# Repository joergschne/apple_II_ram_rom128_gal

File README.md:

# Apple II 128K RAM + ROM Card - Dual GAL

APPLE II forever!

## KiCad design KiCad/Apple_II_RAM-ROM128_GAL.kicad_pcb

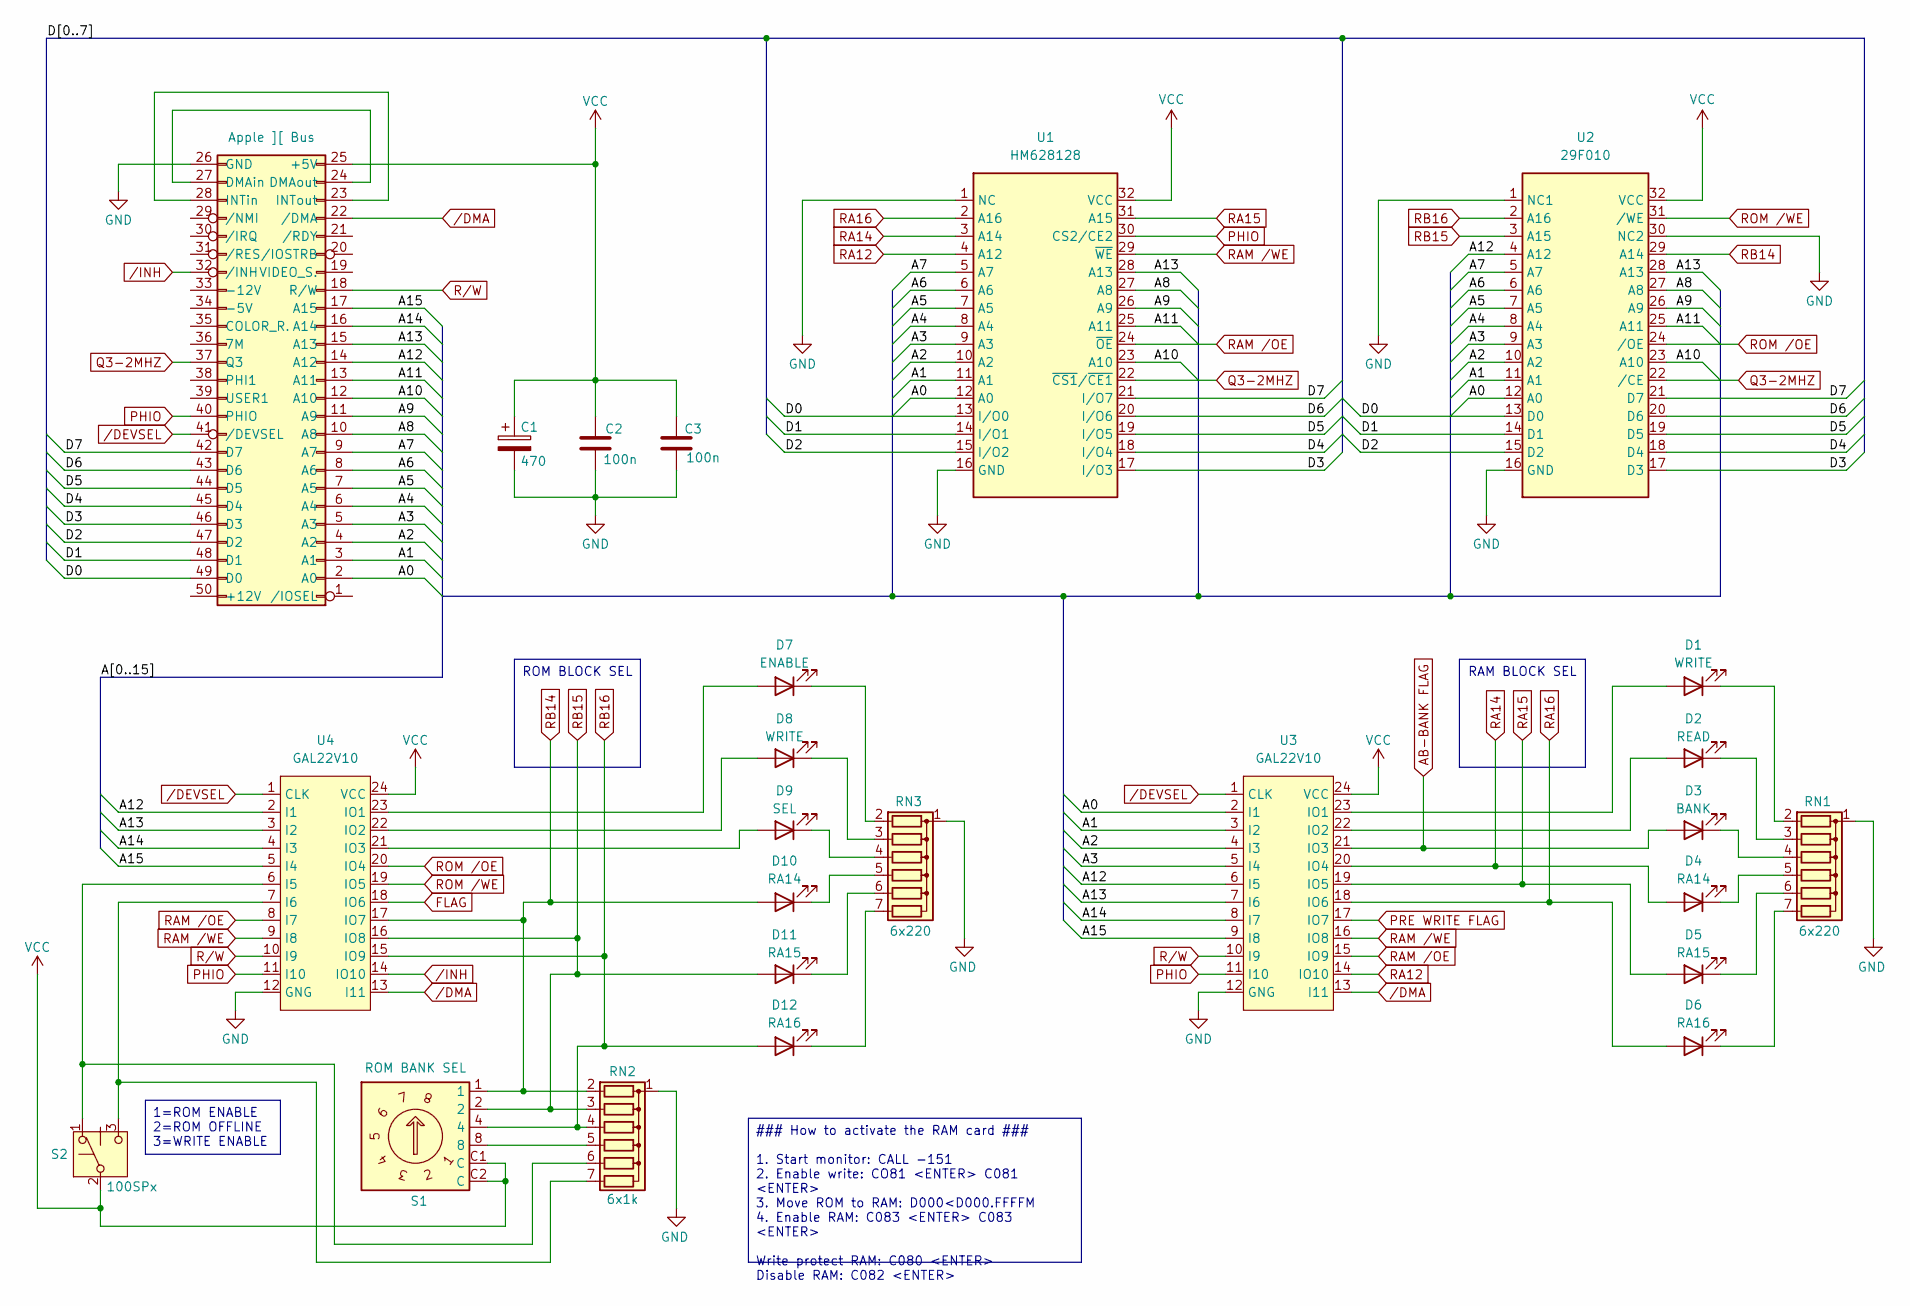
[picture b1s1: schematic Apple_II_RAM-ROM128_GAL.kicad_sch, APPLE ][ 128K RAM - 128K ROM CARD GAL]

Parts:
C1: 470; CP_Radial_D5.0mm_P2.50mm
C2, C3: 100n; C_Rect_L7.0mm_W2.0mm_P5.00mm
D1, D8: WRITE; LED_WP1503CB_GD
D2: READ; LED_WP1503CB_GD
D3: BANK; LED_WP1503CB_GD
D4, D10: RA14; LED_WP1503CB_GD
D5, D11: RA15; LED_WP1503CB_GD
D6, D12: RA16; LED_WP1503CB_GD
D7: ENABLE; LED_WP1503CB_GD
D9: SEL; LED_WP1503CB_GD
J1: Apple ][ Bus
RN1, RN3: 6x220; R_Array_SIP7
RN2: 6x1k; R_Array_SIP7
S1: ROM BANK SEL; R-ENC-42842752091X_10POS
S2: 100SPx; SW_100SP1T2B4M6QE
U1: HM628128; DIP-32_W15.24mm_LongPads
U2: 29F010; DIP-32_W15.24mm_LongPads
U3, U4: GAL22V10; DIP-24_W7.62mm_LongPads

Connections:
/A0: J1.2 (A0), U1.12 (A0), U2.12 (A0), U3.2 (I1)
/A1: J1.3 (A1), U1.11 (A1), U2.11 (A1), U3.3 (I2)
/A2: J1.4 (A2), U1.10 (A2), U2.10 (A2), U3.4 (I3)
/A3: J1.5 (A3), U1.9 (A3), U2.9 (A3), U3.5 (I4)
/A4: J1.6 (A4), U1.8 (A4), U2.8 (A4)
/A5: J1.7 (A5), U1.7 (A5), U2.7 (A5)
/A6: J1.8 (A6), U1.6 (A6), U2.6 (A6)
/A7: J1.9 (A7), U1.5 (A7), U2.5 (A7)
/A8: J1.10 (A8), U1.27 (A8), U2.27 (A8)
/A9: J1.11 (A9), U1.26 (A9), U2.26 (A9)
/A10: J1.12 (A10), U1.23 (A10), U2.23 (A10)
/A11: J1.13 (A11), U1.25 (A11), U2.25 (A11)
/A12: J1.14 (A12), U2.4 (A12), U3.6 (I5), U4.2 (I1)
/A13: J1.15 (A13), U1.28 (A13), U2.28 (A13), U3.7 (I6), U4.3 (I2)
/A14: J1.16 (A14), U3.8 (I7), U4.4 (I3)
/A15: J1.17 (A15), U3.9 (I8), U4.5 (I4)
/D0: J1.49 (D0), U1.13 (I/O0), U2.13 (D0)
/D1: J1.48 (D1), U1.14 (I/O1), U2.14 (D1)
/D2: J1.47 (D2), U1.15 (I/O2), U2.15 (D2)
/D3: J1.46 (D3), U1.17 (I/O3), U2.17 (D3)
/D4: J1.45 (D4), U1.18 (I/O4), U2.18 (D4)
/D5: J1.44 (D5), U1.19 (I/O5), U2.19 (D5)
/D6: J1.43 (D6), U1.20 (I/O6), U2.20 (D6)
/D7: J1.42 (D7), U1.21 (I/O7), U2.21 (D7)
AB-BANK FLAG: D3.2 (A), U3.21 (IO3)
FLAG: U4.18 (IO6)
GND: C1.2, C2.2, C3.2, J1.26 (GND), RN1.1 (common), RN2.1 (common), RN3.1 (common), U1.1 (NC), U1.16 (GND), U2.1 (NC1), U2.16 (GND), U2.30 (NC2), U3.12 (GNG), U4.12 (GNG)
unnamed: D1.2 (A), U3.23 (IO1)
unnamed: D1.1 (K), RN1.2 (R1)
unnamed: D2.2 (A), U3.22 (IO2)
unnamed: D2.1 (K), RN1.3 (R2)
unnamed: D3.1 (K), RN1.4 (R3)
unnamed: D4.1 (K), RN1.5 (R4)
unnamed: D5.1 (K), RN1.6 (R5)
unnamed: D6.1 (K), RN1.7 (R6)
unnamed: D7.2 (A), U4.23 (IO1)
unnamed: D7.1 (K), RN3.2 (R1)
unnamed: D8.2 (A), U4.22 (IO2)
unnamed: D8.1 (K), RN3.3 (R2)
unnamed: D9.2 (A), U4.21 (IO3)
unnamed: D9.1 (K), RN3.4 (R3)
unnamed: D10.1 (K), RN3.5 (R4)
unnamed: D11.1 (K), RN3.6 (R5)
unnamed: D12.1 (K), RN3.7 (R6)
unnamed: J1.24 (DMAout), J1.27 (DMAin)
unnamed: J1.23 (INTout), J1.28 (INTin)
unnamed 46: RN2.5 (R4), S1.8; also elsewhere on the board
unnamed: RN2.6 (R5), S2.1, U4.6 (I5)
unnamed: RN2.7 (R6), S2.3, U4.7 (I6)
PHIO: J1.40 (PHIO), U1.30 (CS2/CE2), U3.11 (I10), U4.11 (I10)
PRE WRITE FLAG: U3.17 (IO7)
Q3-2MHZ: J1.37 (Q3), U1.22 (~CS1/~CE1), U2.22 (/CE)
RA12: U1.4 (A12), U3.14 (IO10)
RA14: D4.2 (A), U1.3 (A14), U3.20 (IO4)
RA15: D5.2 (A), U1.31 (A15), U3.19 (IO5)
RA16: D6.2 (A), U1.2 (A16), U3.18 (IO6)
RAM /OE: U1.24 (~OE), U3.15 (IO9), U4.8 (I7)
RAM /WE: U1.29 (~WE), U3.16 (IO8), U4.9 (I8)
RB14: D10.2 (A), RN2.2 (R1), S1.1, U2.29 (A14), U4.17 (IO7); also elsewhere on the board
RB15: D11.2 (A), RN2.3 (R2), S1.2, U2.3 (A15), U4.16 (IO8); also elsewhere on the board
RB16: D12.2 (A), RN2.4 (R3), S1.4, U2.2 (A16), U4.15 (IO9); also elsewhere on the board
ROM /OE: U2.24 (/OE), U4.20 (IO4)
ROM /WE: U2.31 (/WE), U4.19 (IO5)
R/W: J1.18 (R/W), U3.10 (I9), U4.10 (I9)
VCC: C1.1, C2.1, C3.1, J1.25 (+5V), S1.C1 (C), S1.C2 (C), S2.2, U1.32 (VCC), U2.32 (VCC), U3.24 (VCC), U4.24 (VCC); also elsewhere on the board
/DEVSEL: J1.41 (/DEVSEL), U3.1 (CLK), U4.1 (CLK)
/DMA: J1.22 (/DMA), U3.13 (I11), U4.13 (I11)
/INH: J1.32 (/INH), U4.14 (IO10)

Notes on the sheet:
RAM BLOCK SEL
ROM BLOCK SEL
1=ROM ENABLE 2=ROM OFFLINE 3=WRITE ENABLE
### How to activate the RAM card ### 1. Start monitor: CALL -151 2. Enable write: CO81 <ENTER> C081 <ENTER> 3. Move ROM to RAM: D000<D000.FFFFM 4. Enable RAM: C083 <ENTER> C083 <ENTER> Write protect RAM: C080 <ENTER> Disable RAM: C082 <ENTER>

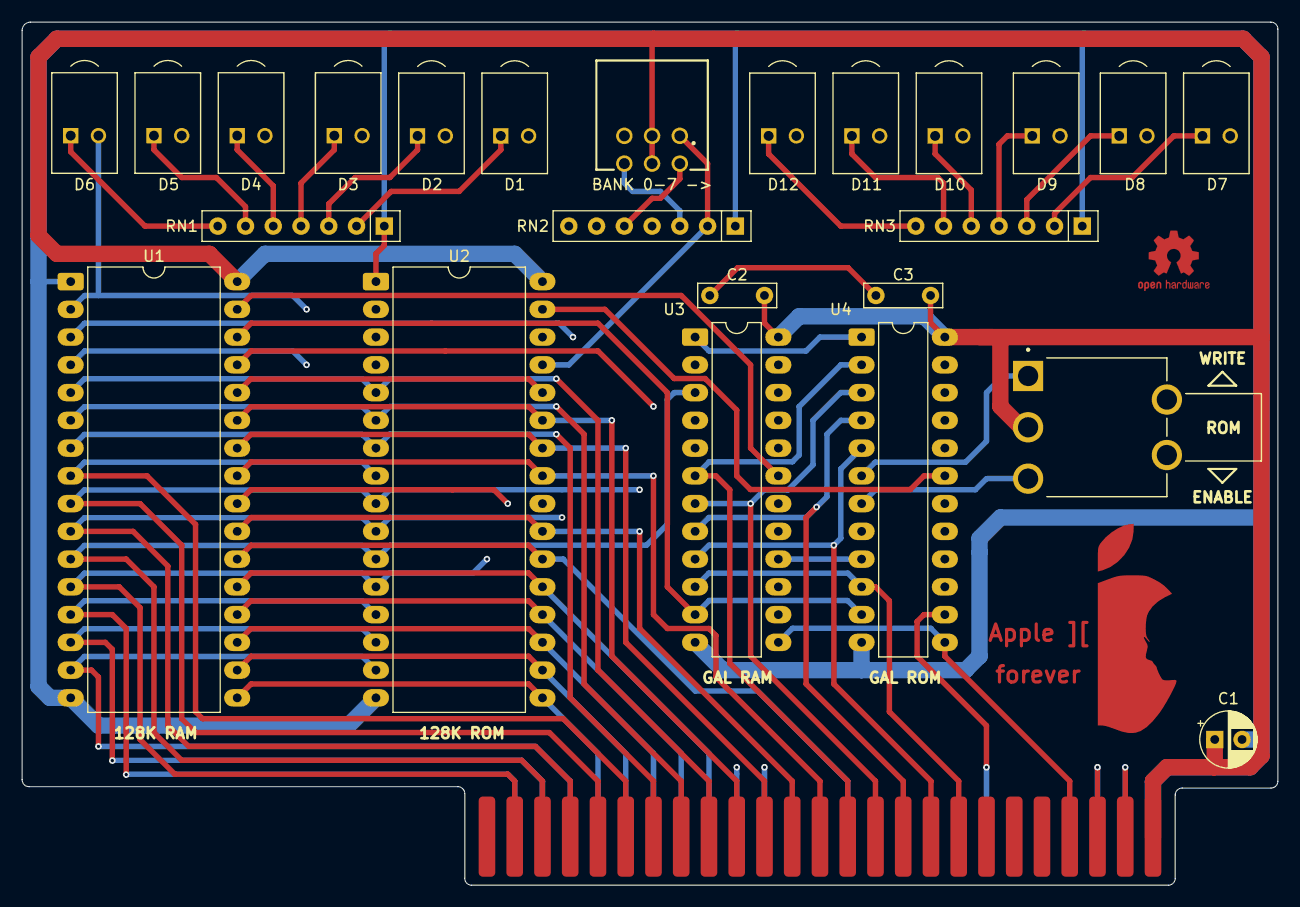
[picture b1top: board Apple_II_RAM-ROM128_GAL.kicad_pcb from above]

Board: 4 copper layers, 114.9 x 79.0 mm, 29 parts (1 on the bottom side), 66 nets.

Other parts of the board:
APPLE, APPLE1: LOGO
BANK 0-7 ->: ROM BANK SEL; R-ENC-42842752091X_10POS
OSHW1: OSHW-Logo2_7.3x6mm_Copper
SATURN: LOGO

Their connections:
unnamed 46: BANK 0-7 ->.8; also elsewhere on the board
RB14: BANK 0-7 ->.1; also elsewhere on the board
RB15: BANK 0-7 ->.2; also elsewhere on the board
RB16: BANK 0-7 ->.4; also elsewhere on the board
VCC: BANK 0-7 ->.C1 (C), BANK 0-7 ->.C2 (C); also elsewhere on the board

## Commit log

2025-03-06 design update
